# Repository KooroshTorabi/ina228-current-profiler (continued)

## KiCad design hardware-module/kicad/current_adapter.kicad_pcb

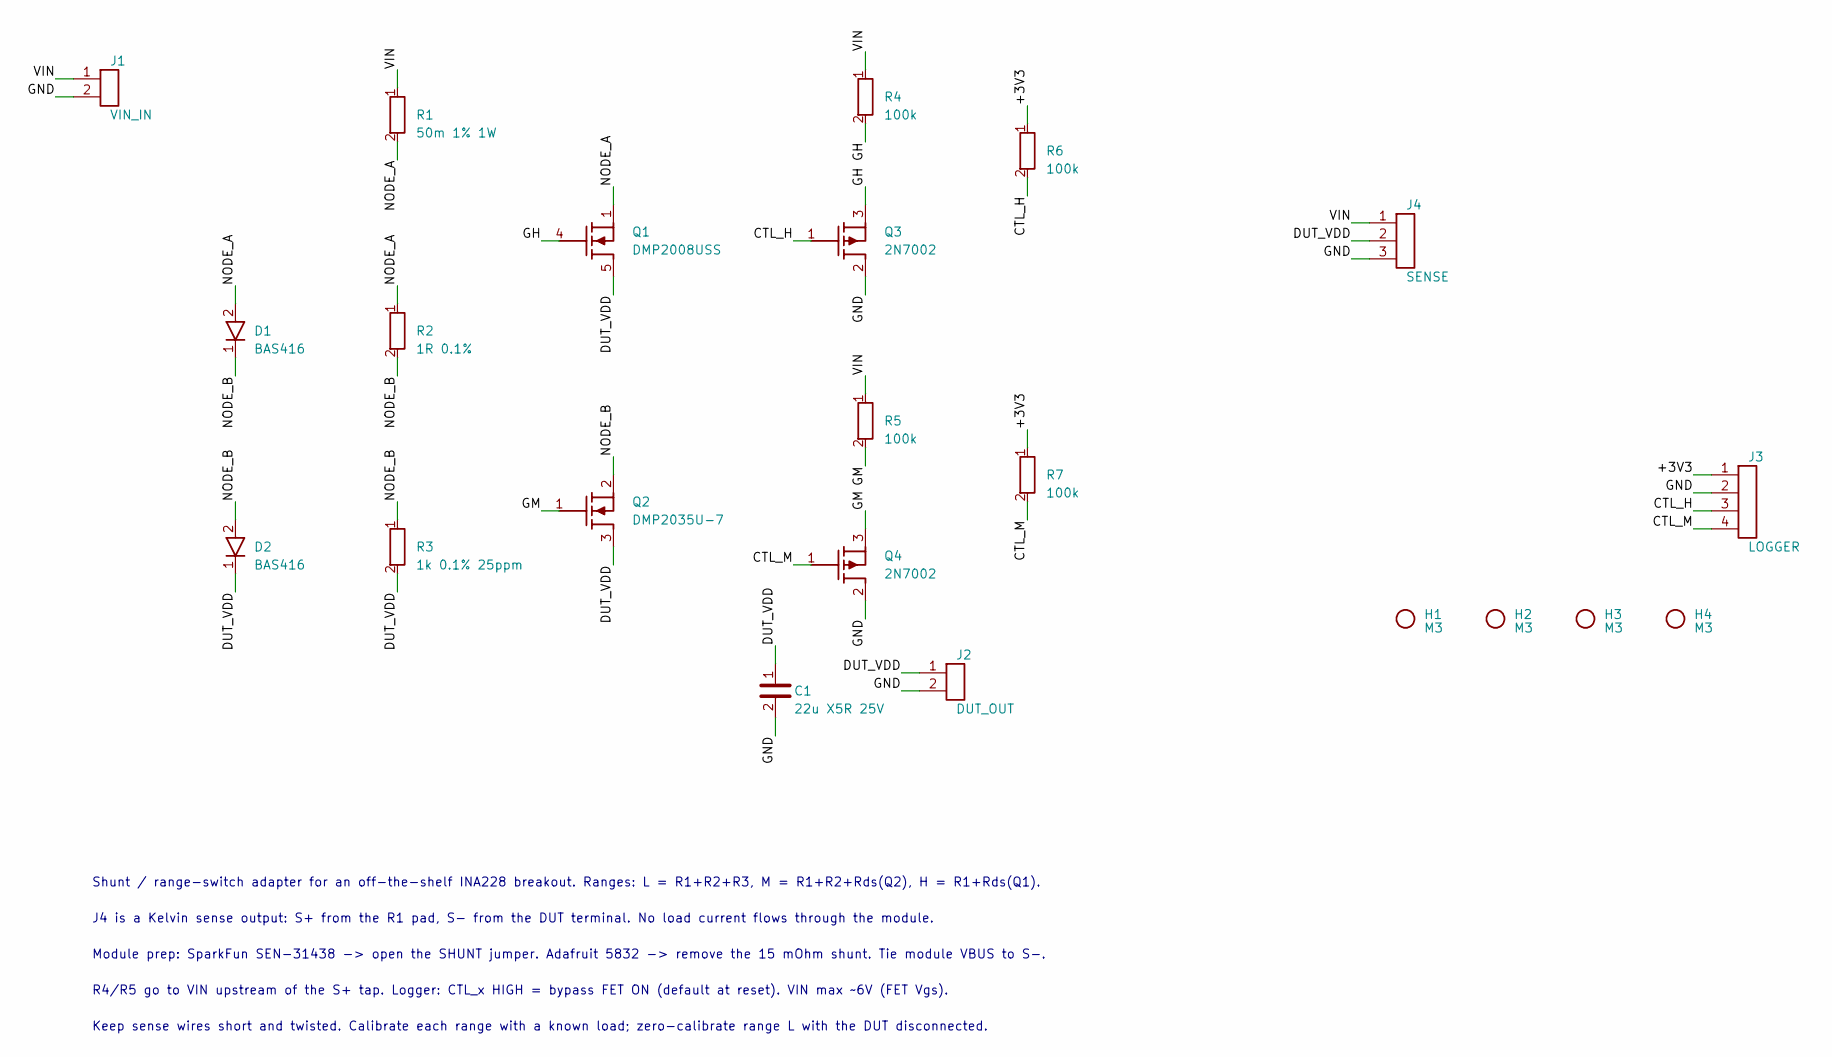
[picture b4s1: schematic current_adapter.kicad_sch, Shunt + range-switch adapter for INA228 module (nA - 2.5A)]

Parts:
C1: 22u X5R 25V; C_1206_3216Metric
D1, D2: BAS416; D_SOD-323
H1, H2, H3, H4: M3; MountingHole_3.2mm_M3
J1: VIN_IN; TerminalBlock_Phoenix_MKDS-1,5-2-5.08_1x02_P5.08mm_Horizont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
J2: DUT_OUT; TerminalBlock_Phoenix_MKDS-1,5-2-5.08_1x02_P5.08mm_Horizont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
J3: LOGGER; PinHeader_1x04_P2.54mm_Vertical
J4: SENSE; PinHeader_1x03_P2.54mm_Vertical
Q1: DMP2008USS; SOIC-8_3.9x4.9mm_P1.27mm
Q2: DMP2035U-7; SOT-23
Q3, Q4: 2N7002; SOT-23
R1: 50m 1% 1W; R_2512_6332Metric
R2: 1R 0.1%; R_1206_3216Metric
R3: 1k 0.1% 25ppm; R_0805_2012Metric
R4, R5, R6, R7: 100k; R_0603_1608Metric

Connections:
+3V3: J3.1, R6.1, R7.1
CTL_H: J3.3, Q3.1 (G), R6.2
CTL_M: J3.4, Q4.1 (G), R7.2
DUT_VDD: C1.1, D2.1 (K), J2.1, J4.2, Q1.5 (D), Q1.6 (D), Q1.7 (D), Q1.8 (D), Q2.3 (D), R3.2
GH: Q1.4 (G), Q3.3 (D), R4.2
GM: Q2.1 (G), Q4.3 (D), R5.2
GND: C1.2, J1.2, J2.2, J3.2, J4.3, Q3.2 (S), Q4.2 (S)
NODE_A: D1.2 (A), Q1.1 (S), Q1.2 (S), Q1.3 (S), R1.2, R2.1
NODE_B: D1.1 (K), D2.2 (A), Q2.2 (S), R2.2, R3.1
VIN: J1.1, J4.1, R1.1, R4.1, R5.1

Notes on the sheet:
Shunt / range-switch adapter for an off-the-shelf INA228 breakout. Ranges: L = R1+R2+R3, M = R1+R2+Rds(Q2), H = R1+Rds(Q1).
J4 is a Kelvin sense output: S+ from the R1 pad, S- from the DUT terminal. No load current flows through the module.
Module prep: SparkFun SEN-31438 -> open the SHUNT jumper. Adafruit 5832 -> remove the 15 mOhm shunt. Tie module VBUS to S-.
R4/R5 go to VIN upstream of the S+ tap. Logger: CTL_x HIGH = bypass FET ON (default at reset). VIN max ~6V (FET Vgs).
Keep sense wires short and twisted. Calibrate each range with a known load; zero-calibrate range L with the DUT disconnected.

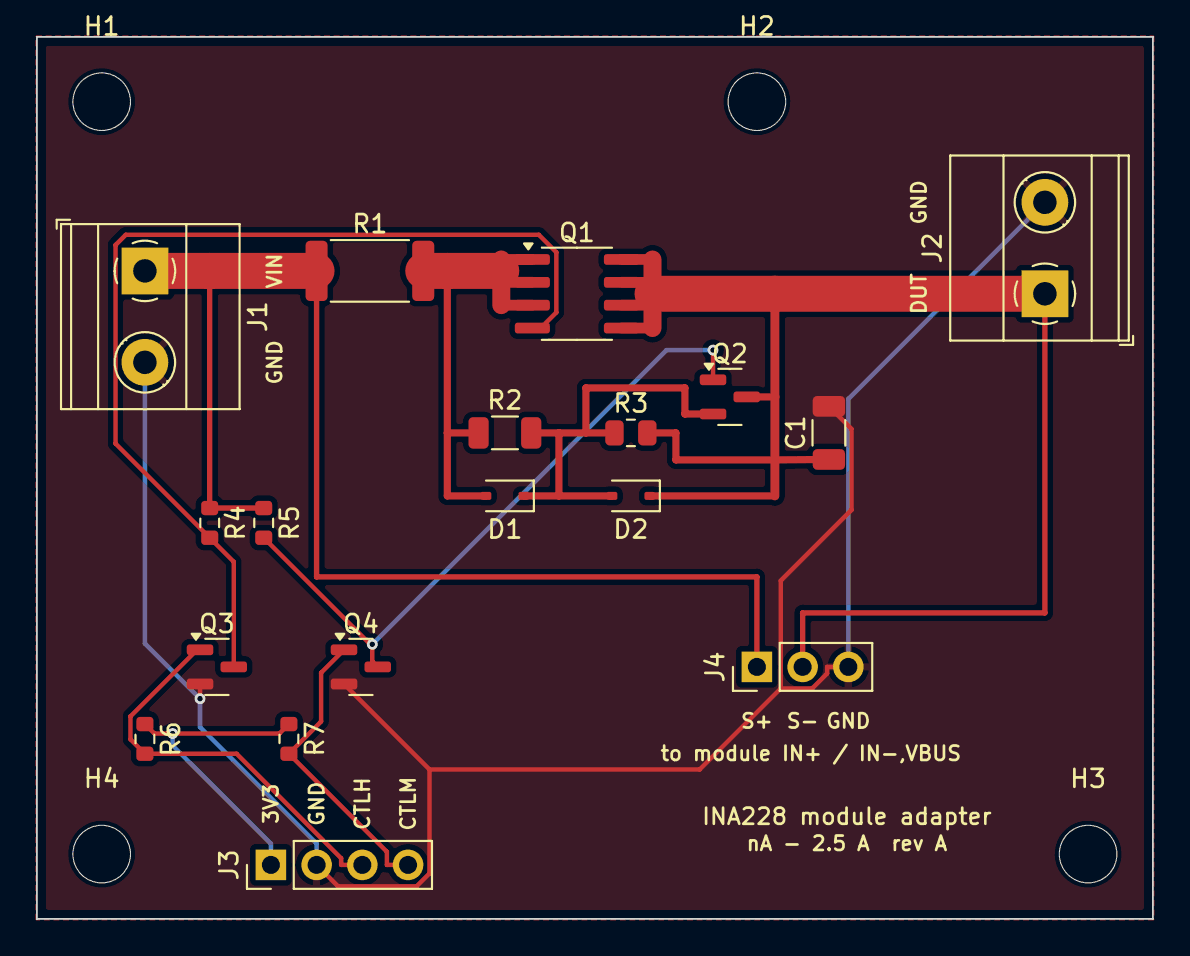
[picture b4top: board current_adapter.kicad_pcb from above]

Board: 2 copper layers, 62.0 x 49.0 mm, 22 parts (0 on the bottom side), 10 nets.

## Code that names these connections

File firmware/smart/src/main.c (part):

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 *
 * The host never switches ranges. It reads one current value (A), one voltage (V)
 * and the integrated charge/energy:
 *   - I2C slave at 0x48 on J3 (PA12 = SDA, PA11 = SCL), register map in README.md
 *   - CSV stream on J3 TX (USART2, 921600 8N1): "t_us,current_A,voltage_V,range"
 *     and text commands on J3 RX (see README.md)
 *
 * Ranging:
 *   - Up, fast:  U3 (comparator) pulls PA0 low when VIN - DUT_VDD exceeds ~32 mV.
 *                The EXTI interrupt steps up one range within about 1 us.
 *   - Up, slow:  a reading above 90 % of the ADC full scale also steps up.
 *   - Down:      when the current would give less than 15 mV in the next lower range
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 *   - After every switch DISCARD conversions are dropped; charge and energy keep
 *                integrating with the last good current across that gap.
 *
 * Pins: PA0 CMP_OUT, PA1 INA ALERT, PA2/PA3 USART2, PA4 CTL_H, PA5 CTL_M, PA6 LED,
 *       PB6/PB7 I2C1 (INA228), PA11/PA12 I2C2 (host), PA13/PA14 SWD.
 */
#include <stdint.h>
#include <string.h>
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    /* CTL_H, CTL_M: drive HIGH first (range H, same as the pull-ups), then outputs; LED output */
    GPIOA->BSRR = (1u << 4) | (1u << 5);
    GPIOA->MODER = (GPIOA->MODER & ~((3u << 8) | (3u << 10) | (3u << 12) | (3u << 0) | (3u << 2)))
                 | (1u << 8) | (1u << 10) | (1u << 12);           /* PA0, PA1 inputs */
    /* PA2/PA3 USART2 AF1 */
    GPIOA->MODER = (GPIOA->MODER & ~((3u << 4) | (3u << 6))) | (2u << 4) | (2u << 6);
    GPIOA->AFR[0] = (GPIOA->AFR[0] & ~((0xFu << 8) | (0xFu << 12))) | (1u << 8) | (1u << 12);
    /* PA11/PA12 I2C2 AF6 open drain */
    GPIOA->OTYPER |= (1u << 11) | (1u << 12);
    GPIOA->MODER = (GPIOA->MODER & ~((3u << 22) | (3u << 24))) | (2u << 22) | (2u << 24);
    GPIOA->AFR[1] = (GPIOA->AFR[1] & ~((0xFu << 12) | (0xFu << 16))) | (6u << 12) | (6u << 16);
    /* PB6/PB7 I2C1 AF6 open drain (PB8 bonded to PB7, PB3-5 to PB6: those stay analog) */
    GPIOB->OTYPER |= (1u << 6) | (1u << 7);
    GPIOB->MODER = (GPIOB->MODER & ~((3u << 12) | (3u << 14))) | (2u << 12) | (2u << 14);
    GPIOB->AFR[0] = (GPIOB->AFR[0] & ~((0xFu << 24) | (0xFu << 28))) | (6u << 24) | (6u << 28);
    /* comparator: EXTI line 0 = PA0, falling edge */
    EXTI->EXTICR[0] &= ~0xFFu;
    EXTI->FTSR1 |= EXTI_FTSR1_FT0;
    NVIC_SetPriority(EXTI0_1_IRQn, 0);
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            if ((uint32_t)(micros() - retry) > 500000u) { retry = micros(); ina_ok = (uint8_t)ina_init(); GPIOA->ODR ^= (1u << 6); publish(0, 0); }
        } else {
            ina_set_adcrange(range);               /* after a fast step-up from the comparator */
            if (!(GPIOA->IDR & (1u << 1))) sample();   /* ALERT low: conversion ready */
            else if ((uint32_t)(micros() - t_prev) > 1000000u) { ina_ok = (uint8_t)ina_init(); t_prev = micros(); }
        }
        if (rx_ready) { do_command(rxline); rx_len = 0; rx_ready = 0; }
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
